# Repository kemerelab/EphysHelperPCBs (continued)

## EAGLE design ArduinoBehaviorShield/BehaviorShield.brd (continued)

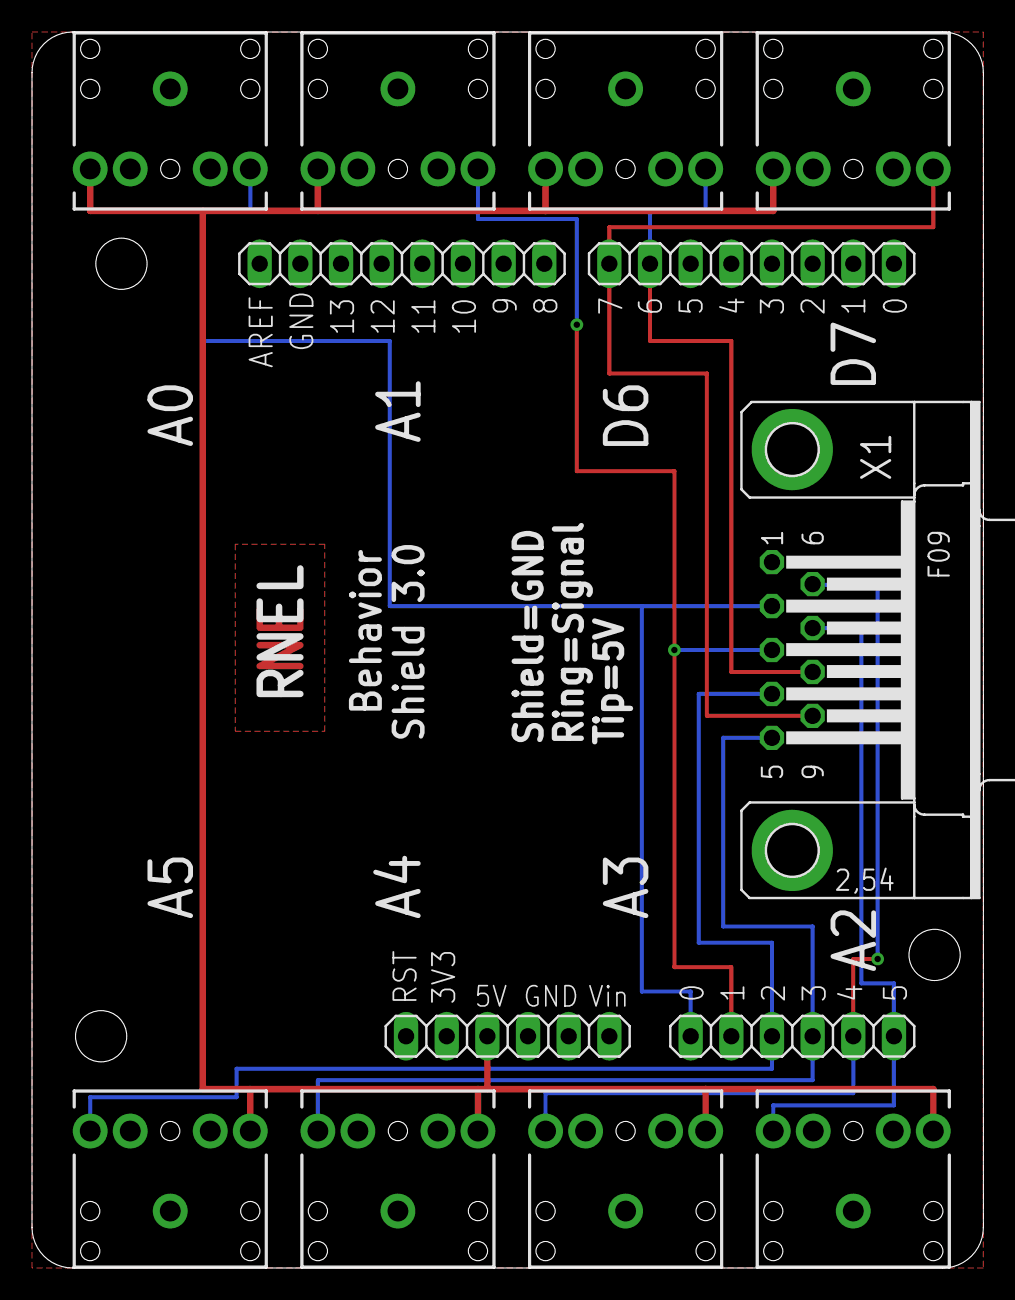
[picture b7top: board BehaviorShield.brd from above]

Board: 2 copper layers, 59.4 x 77.2 mm, 13 parts (0 on the bottom side), 10 nets.

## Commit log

2016-05-12 Added .gitignore
2016-05-17 Added a bunch of files
2016-05-18 Updated, almost finished interface board
2016-05-29 Updated Neuralynx breakout board before manufacturing
2016-05-29 Added NeuralynxBreakout manufacturing files. Added Mill-Max version of SpikeGadgets EIB.
2016-05-29 Updated Readme and added License
2016-08-20 Added RightAngle 32 ch headstage and Omnetics-to-right-angle adaptors for 1 and 2 headstages
2016-08-20 Added EIB with two Hirose connectors defined as individual parts for manufacturing
2016-08-25 Added Plating Board for Mill-Max compatible EIB (needs to be narrow to fit).
2016-12-29 Added beam break - this is the version that we send to Seeed Studio's Fusion PCBA service
2017-02-14 Added Shayoks stim neuralynx EIB
2017-02-15 Updated stim board
2017-02-25 Added 128 pin circular EIB
2017-03-09 Updated design to fix error
2017-03-09 Added zip archive of manufacturing files
2018-04-28 Added Neuronexus interface board
2018-07-19 Three updates for Circular EIB: - Add library with the radial tetrode configuration (1.5 in diameter) in 0.3 mm and 0.25 mm tetrode holes - Update CircleEIB files with 0.3 mm tetrode hole specificati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
2019-01-07 Added some arduino shields with 1/8 inch audio connectors for IO
2020-10-09 Added a 4 BNC breakout for rapidly switching illumination for widefield imaging
2020-10-29 Added widefield controller firmware
2020-11-19 Updated firmware for widefield controller
2020-11-19 Updated firmware
2020-11-28 Updated WidefieldController board to be smaller
2022-03-08 Updated solder paste to be little squares for center pads.
2023-07-03 Many designs added
